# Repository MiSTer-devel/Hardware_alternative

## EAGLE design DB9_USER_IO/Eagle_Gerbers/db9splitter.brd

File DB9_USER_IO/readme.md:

This is an alternative to the USB 3.0 connector. It's a DB9 port, compatible with Genesis
gamepads. Also each pin of the FPGA is protected with BAT54S diodes, so it's not possible
less than 0V or more than 3.3V enter to the FPGA. Included the Genesis core fork.

The cores with DB9 support are available here:
https://github.com/antoniovillena/MiSTer_DB9

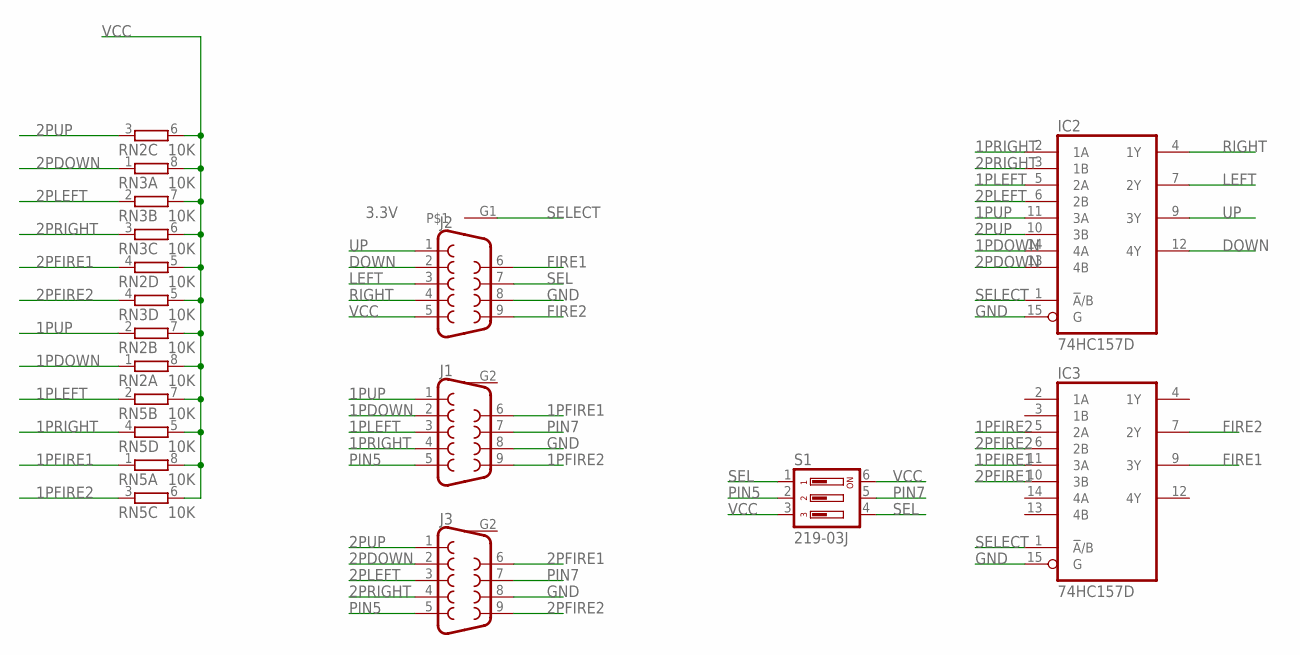
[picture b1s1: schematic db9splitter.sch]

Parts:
IC2, IC3: 74HC157D; SO16
J1, J3: SPARKFUN-CONNECTORS_DB9MALE; SPARKFUN-CONNECTORS_DB9_MALE
J2: DB9FEMALE; DB9
RN2, RN3, RN5: 10K; 0603-ARC
S1: 219-03J; CTS-219-03J

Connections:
1PDOWN: IC2.14 (4A), J1.2, RN2.1
1PFIRE1: IC3.11 (3A), J1.6, RN5.1
1PFIRE2: IC3.5 (2A), J1.9, RN5.3 (1)
1PLEFT: IC2.5 (2A), J1.3, RN5.2 (1)
1PRIGHT: IC2.2 (1A), J1.4, RN5.4 (1)
1PUP: IC2.11 (3A), J1.1, RN2.2 (1)
2PDOWN: IC2.13 (4B), J3.2, RN3.1
2PFIRE1: IC3.10 (3B), J3.6, RN2.4 (1)
2PFIRE2: IC3.6 (2B), J3.9, RN3.4 (1)
2PLEFT: IC2.6 (2B), J3.3, RN3.2 (1)
2PRIGHT: IC2.3 (1B), J3.4, RN3.3 (1)
2PUP: IC2.10 (3B), J3.1, RN2.3 (1)
DOWN: IC2.12 (4Y), J2.2
FIRE1: IC3.9 (3Y), J2.6
FIRE2: IC3.7 (2Y), J2.9
GND: IC2.8 (GND), IC2.15 (G), IC3.8 (GND), IC3.15 (G), J1.8, J2.8, J3.8
LEFT: IC2.7 (2Y), J2.3
PIN5: J1.5, J3.5, S1.2
PIN7: J1.7, J3.7, S1.5
RIGHT: IC2.4 (1Y), J2.4
SEL: J2.7, S1.1, S1.4
SELECT: IC2.1 (!A!/B), IC3.1 (!A!/B), J2.G1
UP: IC2.9 (3Y), J2.1
VCC: IC2.16 (VCC), IC3.16 (VCC), J2.5, RN2.5 (2), RN2.6 (2), RN2.7 (2), RN2.8 (2), RN3.5 (2), RN3.6 (2), RN3.7 (2), RN3.8 (2), RN5.5 (2), RN5.6 (2), RN5.7 (2), RN5.8 (2), S1.3, S1.6

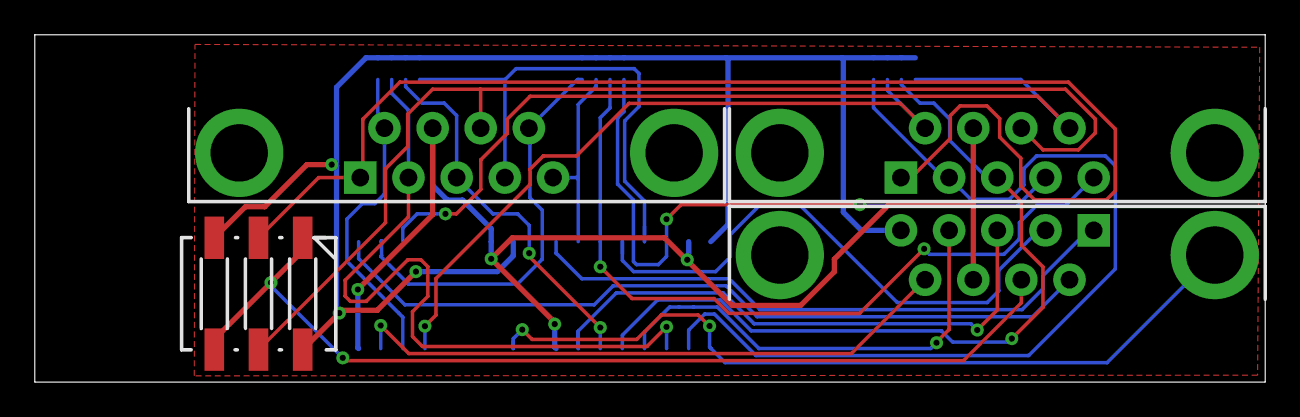
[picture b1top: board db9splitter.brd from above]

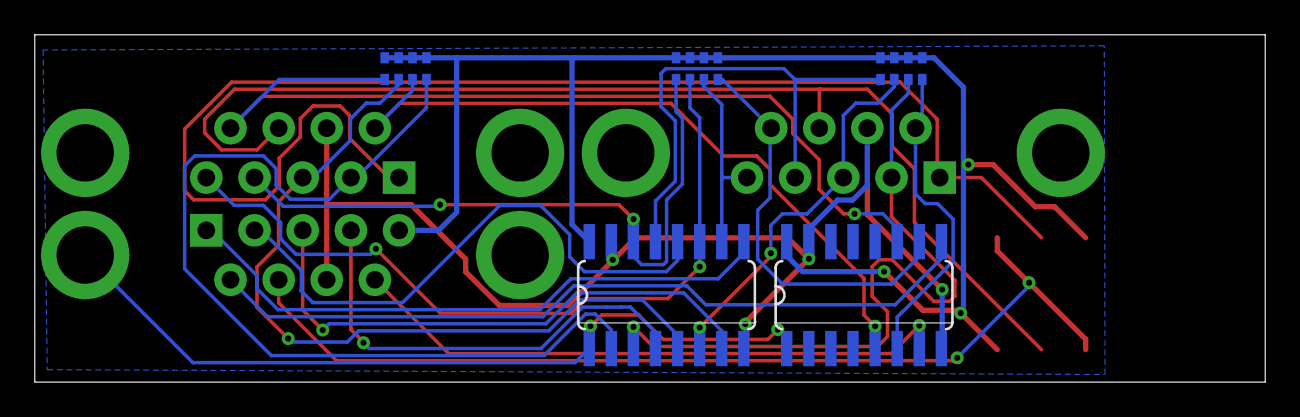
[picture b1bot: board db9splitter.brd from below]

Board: 2 copper layers, 70.7 x 20.0 mm, 9 parts (5 on the bottom side), 24 nets.

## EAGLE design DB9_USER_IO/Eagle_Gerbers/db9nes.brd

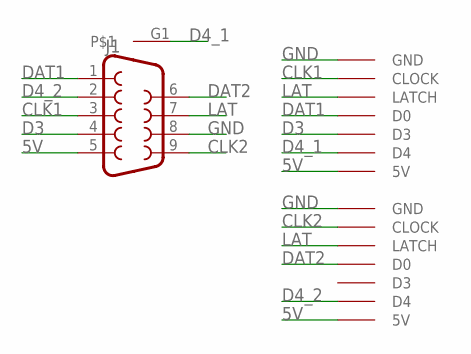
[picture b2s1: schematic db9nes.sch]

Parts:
J1: DB9FEMALE; DB9
U$1, U$2: NESCONNNO_TABS; NESCONN_NO_TABS

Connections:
5V: J1.5, U$1.5V, U$2.5V
CLK1: J1.3, U$2.CLOCK
CLK2: J1.9, U$1.CLOCK
D3: J1.4, U$2.D3
D4_1: J1.G1, U$2.D4
D4_2: J1.2, U$1.D4
DAT1: J1.1, U$2.D0
DAT2: J1.6, U$1.D0
GND: J1.8, U$1.GND, U$2.GND
LAT: J1.7, U$1.LATCH, U$2.LATCH

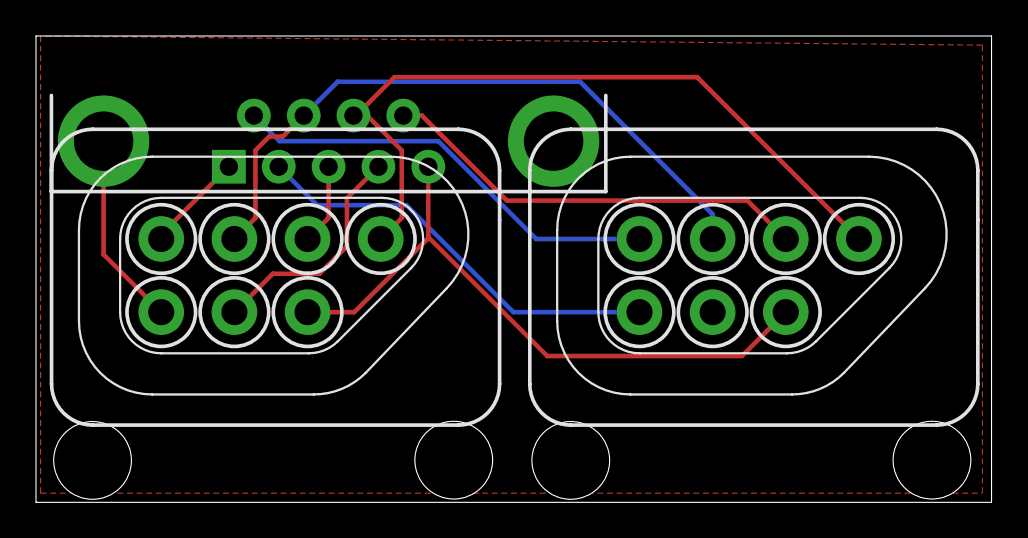
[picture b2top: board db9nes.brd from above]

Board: 2 copper layers, 53.1 x 25.9 mm, 3 parts (0 on the bottom side), 10 nets.

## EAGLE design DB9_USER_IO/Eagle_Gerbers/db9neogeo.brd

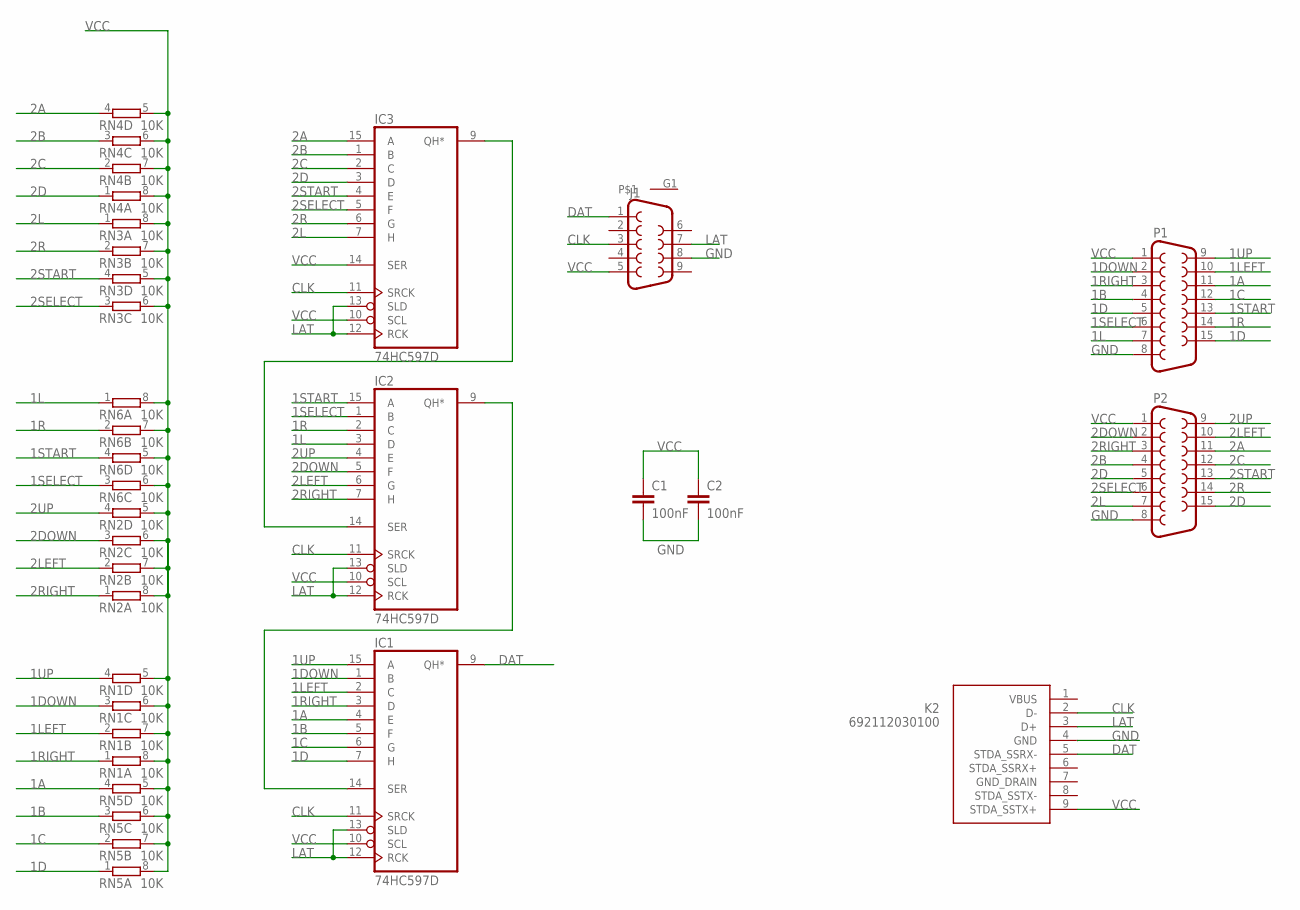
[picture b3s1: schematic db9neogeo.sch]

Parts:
C1, C2: 100nF; C0603K
IC1, IC2, IC3: 74HC597D; SO16
J1: DB9FEMALE; DB9
K2: 692112030100
P1, P2: F15HP
RN1, RN2, RN3, RN4, RN5, RN6: 10K; 0603-ARC

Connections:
1A: IC1.4 (E), P1.11, RN5.4 (1)
1B: IC1.5 (F), P1.4, RN5.3 (1)
1C: IC1.6 (G), P1.12, RN5.2 (1)
1D: IC1.7 (H), P1.5, P1.15, RN5.1
1DOWN: IC1.1 (B), P1.2, RN1.3 (1)
1L: IC2.3 (D), P1.7, RN6.1
1LEFT: IC1.2 (C), P1.10, RN1.2 (1)
1R: IC2.2 (C), P1.14, RN6.2 (1)
1RIGHT: IC1.3 (D), P1.3, RN1.1
1SELECT: IC2.1 (B), P1.6, RN6.3 (1)
1START: IC2.15 (A), P1.13, RN6.4 (1)
1UP: IC1.15 (A), P1.9, RN1.4 (1)
2A: IC3.15 (A), P2.11, RN4.4 (1)
2B: IC3.1 (B), P2.4, RN4.3 (1)
2C: IC3.2 (C), P2.12, RN4.2 (1)
2D: IC3.3 (D), P2.5, P2.15, RN4.1
2DOWN: IC2.5 (F), P2.2, RN2.3 (1)
2L: IC3.7 (H), P2.7, RN3.1
2LEFT: IC2.6 (G), P2.10, RN2.2 (1)
2R: IC3.6 (G), P2.14, RN3.2 (1)
2RIGHT: IC2.7 (H), P2.3, RN2.1
2SELECT: IC3.5 (F), P2.6, RN3.3 (1)
2START: IC3.4 (E), P2.13, RN3.4 (1)
2UP: IC2.4 (E), P2.9, RN2.4 (1)
CLK: IC1.11 (SRCK), IC2.11 (SRCK), IC3.11 (SRCK), J1.3, K2.2 (D-)
DAT: IC1.9 (QH*), J1.1, K2.5 (STDA_SSRX-)
GND: C1.2, C2.2, IC1.8 (GND), IC2.8 (GND), IC3.8 (GND), J1.8, K2.4 (GND), P1.8, P2.8
LAT: IC1.12 (RCK), IC1.13 (SLD), IC2.12 (RCK), IC2.13 (SLD), IC3.12 (RCK), IC3.13 (SLD), J1.7, K2.3 (D+)
unnamed: IC1.14 (SER), IC2.9 (QH*)
unnamed: IC2.14 (SER), IC3.9 (QH*)
VCC: C1.1, C2.1, IC1.10 (SCL), IC1.16 (VCC), IC2.10 (SCL), IC2.16 (VCC), IC3.10 (SCL), IC3.14 (SER), IC3.16 (VCC), J1.5, K2.9 (STDA_SSTX+), P1.1, P2.1, RN1.5 (2), RN1.6 (2), RN1.7 (2), RN1.8 (2), RN2.5 (2), RN2.6 (2), RN2.7 (2), RN2.8 (2), RN3.5 (2), RN3.6 (2), RN3.7 (2), RN3.8 (2), RN4.5 (2), RN4.6 (2), RN4.7 (2), RN4.8 (2), RN5.5 (2), RN5.6 (2), RN5.7 (2), RN5.8 (2), RN6.5 (2), RN6.6 (2), RN6.7 (2), RN6.8 (2)

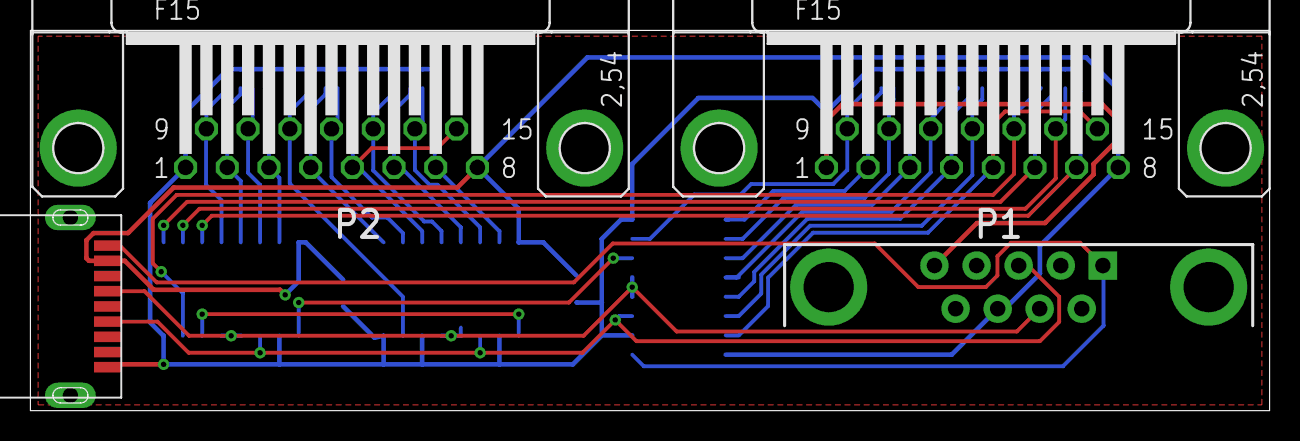
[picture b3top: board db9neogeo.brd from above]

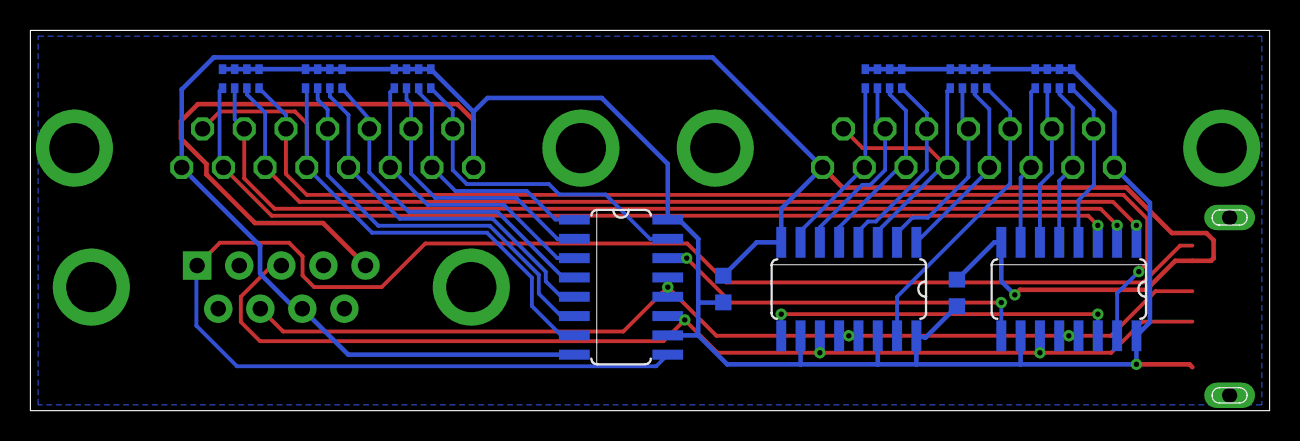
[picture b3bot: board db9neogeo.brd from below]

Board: 2 copper layers, 81.5 x 25.0 mm, 15 parts (11 on the bottom side), 31 nets.

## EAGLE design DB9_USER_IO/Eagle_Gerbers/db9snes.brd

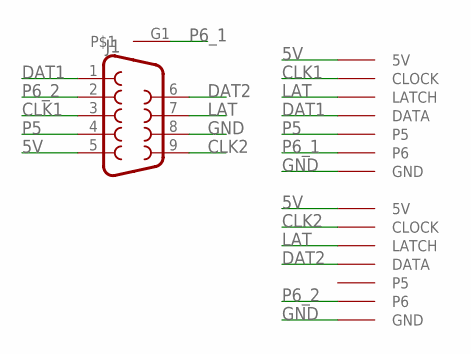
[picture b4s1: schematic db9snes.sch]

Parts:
J1: DB9FEMALE; DB9
U$1, U$3: GAMEPAD-CONN_SNESCONN

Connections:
5V: J1.5, U$1.5V, U$3.5V
CLK1: J1.3, U$3.CLOCK
CLK2: J1.9, U$1.CLOCK
DAT1: J1.1, U$3.DATA
DAT2: J1.6, U$1.DATA
GND: J1.8, U$1.GND, U$3.GND
LAT: J1.7, U$1.LATCH, U$3.LATCH
P5: J1.4, U$3.P5
P6_1: J1.G1, U$3.P6
P6_2: J1.2, U$1.P6

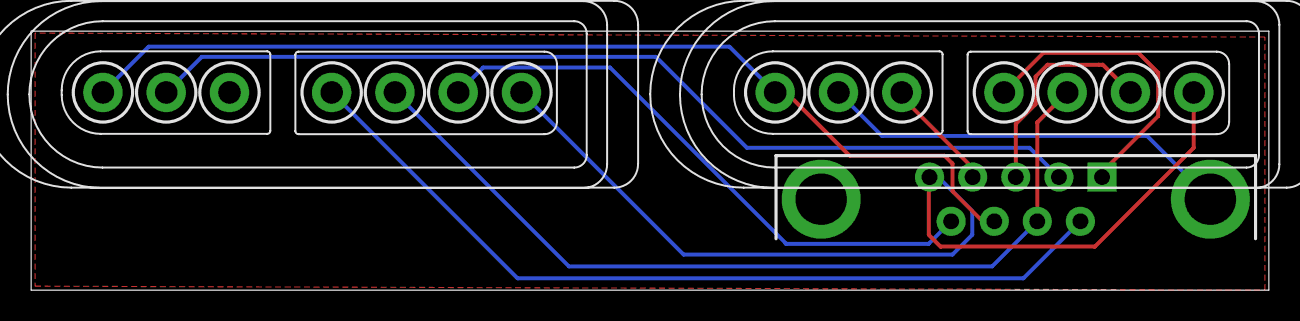
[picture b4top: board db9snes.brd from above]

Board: 2 copper layers, 79.5 x 16.6 mm, 3 parts (0 on the bottom side), 10 nets.

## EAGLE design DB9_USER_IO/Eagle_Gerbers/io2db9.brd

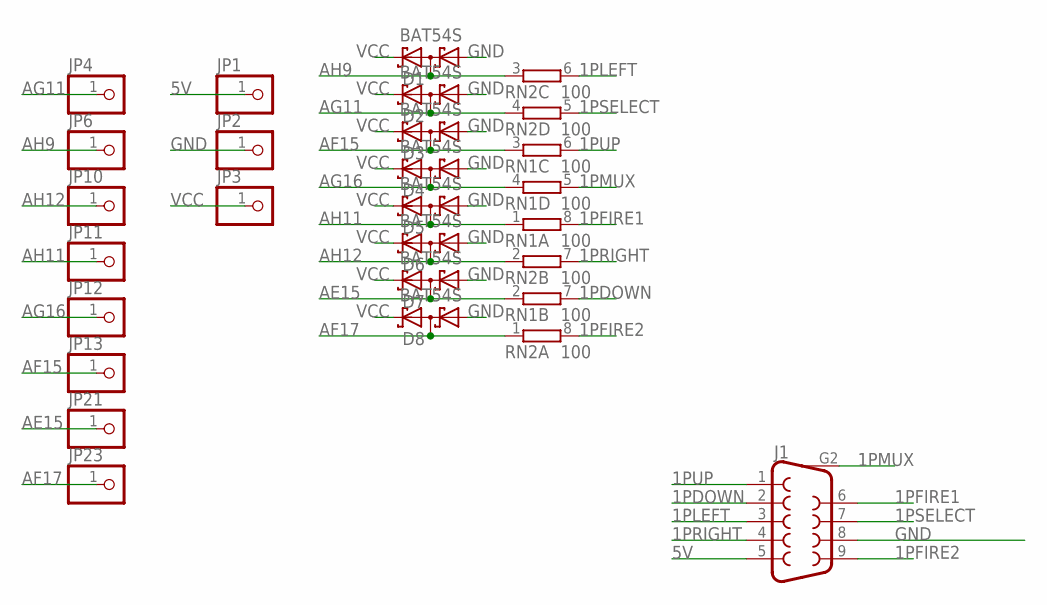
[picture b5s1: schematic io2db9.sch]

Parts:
D1, D2, D3, D4, D5, D6, D7, D8: BAT54S; SOT23
J1: SPARKFUN-CONNECTORS_DB9MALE; SPARKFUN-CONNECTORS_DB9_MALE
JP1, JP2, JP3, JP4, JP6, JP10, JP11, JP12, JP13, JP21, JP23: PINHD-1X1; 1X01
RN1, RN2: 100; 0603-ARC

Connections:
1PDOWN: J1.2, RN1.7 (2)
1PFIRE1: J1.6, RN1.8 (2)
1PFIRE2: J1.9, RN2.8 (2)
1PLEFT: J1.3, RN2.6 (2)
1PMUX: J1.G2 (10), RN1.5 (2)
1PRIGHT: J1.4, RN2.7 (2)
1PSELECT: J1.7, RN2.5 (2)
1PUP: J1.1, RN1.6 (2)
5V: J1.5, JP1.1
AE15: D7.3 (C1A2), JP21.1, RN1.2 (1)
AF15: D3.3 (C1A2), JP13.1, RN1.3 (1)
AF17: D8.3 (C1A2), JP23.1, RN2.1
AG11: D2.3 (C1A2), JP4.1, RN2.4 (1)
AG16: D4.3 (C1A2), JP12.1, RN1.4 (1)
AH9: D1.3 (C1A2), JP6.1, RN2.3 (1)
AH11: D5.3 (C1A2), JP11.1, RN1.1
AH12: D6.3 (C1A2), JP10.1, RN2.2 (1)
GND: D1.1 (A1), D2.1 (A1), D3.1 (A1), D4.1 (A1), D5.1 (A1), D6.1 (A1), D7.1 (A1), D8.1 (A1), J1.8, JP2.1
VCC: D1.2 (C2), D2.2 (C2), D3.2 (C2), D4.2 (C2), D5.2 (C2), D6.2 (C2), D7.2 (C2), D8.2 (C2), JP3.1

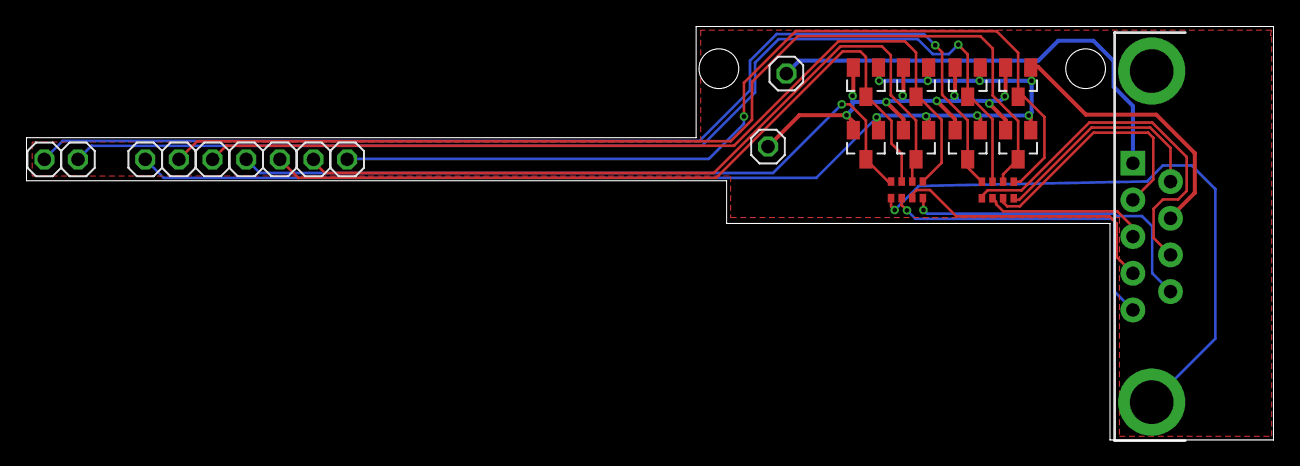
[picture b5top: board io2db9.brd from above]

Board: 2 copper layers, 94.1 x 31.2 mm, 22 parts (0 on the bottom side), 19 nets.

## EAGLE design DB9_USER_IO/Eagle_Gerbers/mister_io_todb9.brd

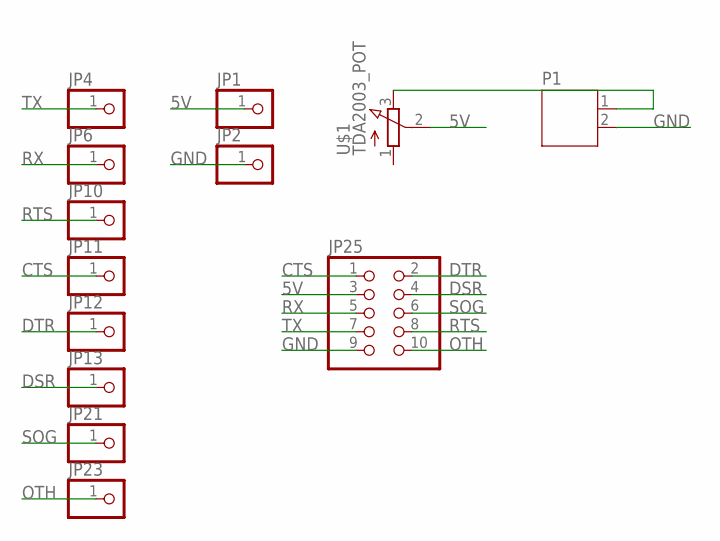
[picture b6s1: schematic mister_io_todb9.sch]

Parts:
JP1, JP2, JP4, JP6, JP10, JP11, JP12, JP13, JP21, JP23: PINHD-1X1; 1X01
JP25: PINHD-2X5; 2X05
P1: JST-PH2
U$1: TDA2003_POT

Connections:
5V: JP1.1, JP25.3, U$1.2 (S)
CTS: JP11.1, JP25.1
DSR: JP13.1, JP25.4
DTR: JP12.1, JP25.2
GND: JP2.1, JP25.9, P1.2
unnamed: P1.1, U$1.3 (E)
OTH: JP23.1, JP25.10
RTS: JP10.1, JP25.8
RX: JP6.1, JP25.5
SOG: JP21.1, JP25.6
TX: JP4.1, JP25.7

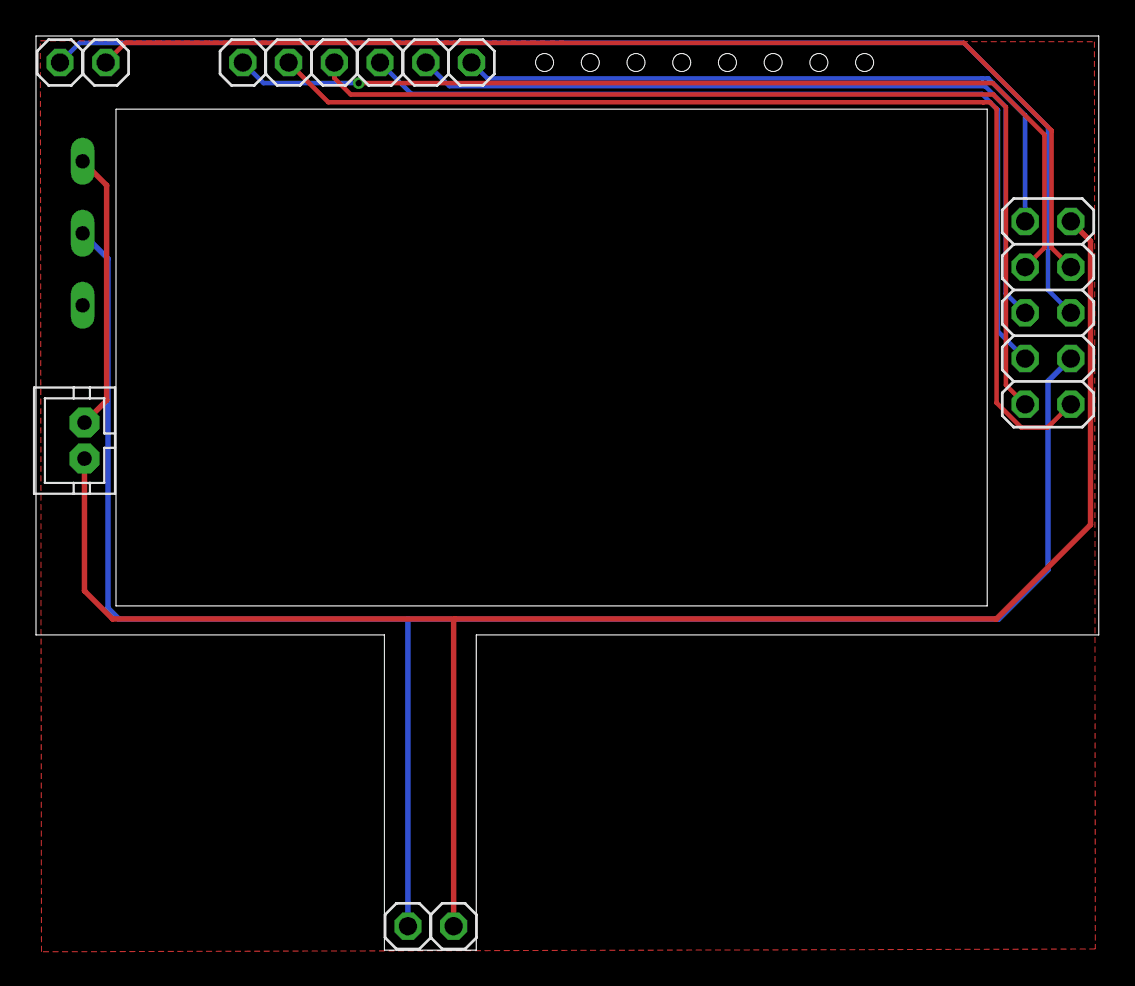
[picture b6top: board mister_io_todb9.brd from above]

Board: 2 copper layers, 59.0 x 50.8 mm, 13 parts (0 on the bottom side), 11 nets.

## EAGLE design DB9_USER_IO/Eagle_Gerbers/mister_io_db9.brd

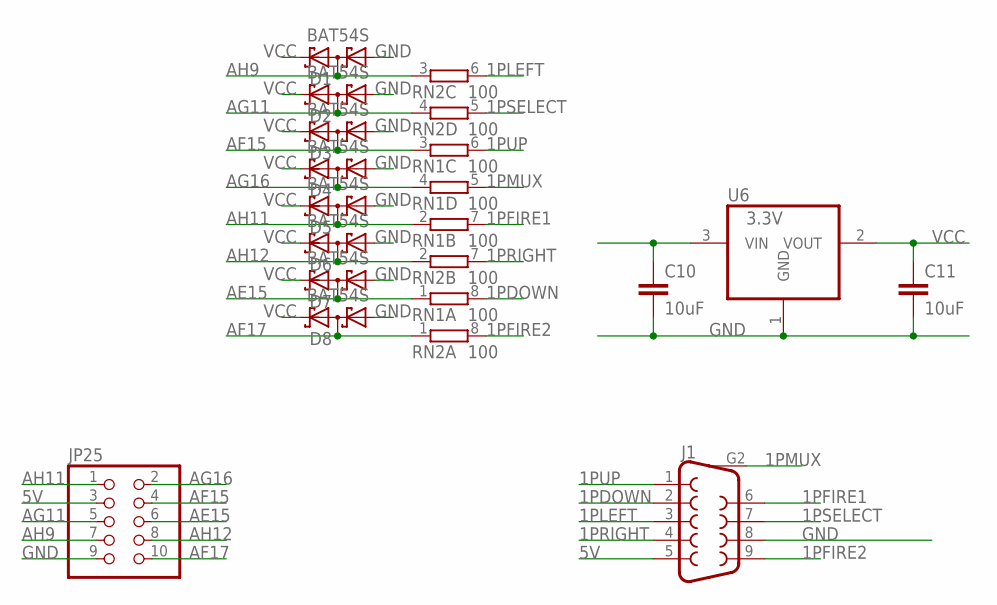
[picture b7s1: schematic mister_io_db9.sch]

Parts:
C10, C11: 10uF; C0603K
D1, D2, D3, D4, D5, D6, D7, D8: BAT54S; SOT23
J1: SPARKFUN-CONNECTORS_DB9MALE; SPARKFUN-CONNECTORS_DB9_MALE
JP25: PINHD-2X5; 2X05
RN1, RN2: 100; 0603-ARC
U6: 3.3V; SOT223

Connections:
1PDOWN: J1.2, RN1.8 (2)
1PFIRE1: J1.6, RN1.7 (2)
1PFIRE2: J1.9, RN2.8 (2)
1PLEFT: J1.3, RN2.6 (2)
1PMUX: J1.G2 (10), RN1.5 (2)
1PRIGHT: J1.4, RN2.7 (2)
1PSELECT: J1.7, RN2.5 (2)
1PUP: J1.1, RN1.6 (2)
5V: C10.1, J1.5, JP25.3, U6.3 (VIN)
AE15: D7.3 (C1A2), JP25.6, RN1.1
AF15: D3.3 (C1A2), JP25.4, RN1.3 (1)
AF17: D8.3 (C1A2), JP25.10, RN2.1
AG11: D2.3 (C1A2), JP25.5, RN2.4 (1)
AG16: D4.3 (C1A2), JP25.2, RN1.4 (1)
AH9: D1.3 (C1A2), JP25.7, RN2.3 (1)
AH11: D5.3 (C1A2), JP25.1, RN1.2 (1)
AH12: D6.3 (C1A2), JP25.8, RN2.2 (1)
GND: C10.2, C11.2, D1.1 (A1), D2.1 (A1), D3.1 (A1), D4.1 (A1), D5.1 (A1), D6.1 (A1), D7.1 (A1), D8.1 (A1), J1.8, JP25.9, U6.1 (GND)
VCC: C11.1, D1.2 (C2), D2.2 (C2), D3.2 (C2), D4.2 (C2), D5.2 (C2), D6.2 (C2), D7.2 (C2), D8.2 (C2), U6.2 (VOUT)

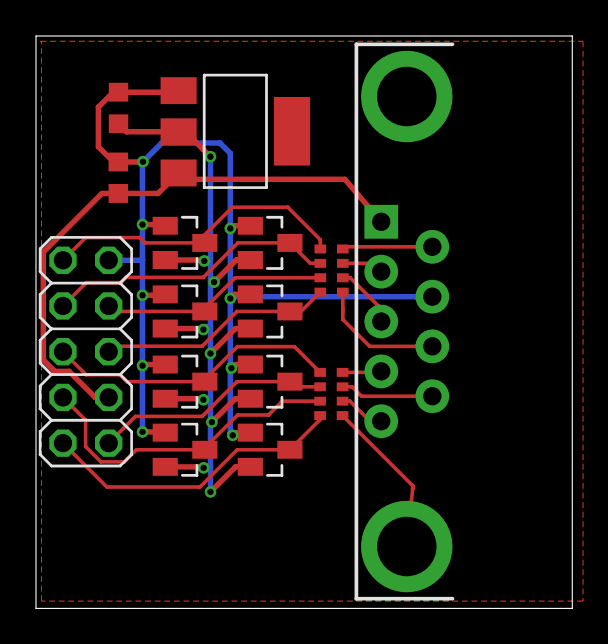
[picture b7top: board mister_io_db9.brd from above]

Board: 2 copper layers, 29.8 x 31.8 mm, 15 parts (0 on the bottom side), 19 nets.

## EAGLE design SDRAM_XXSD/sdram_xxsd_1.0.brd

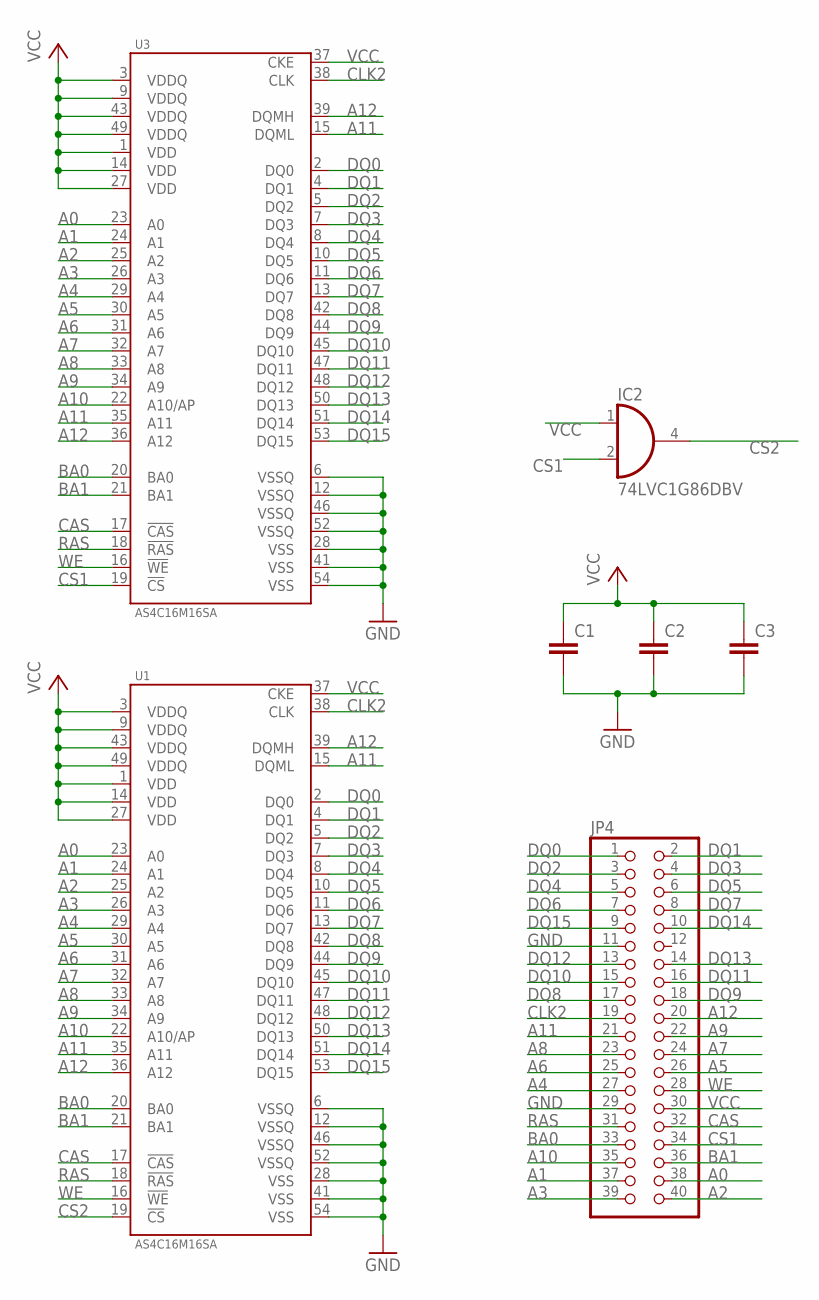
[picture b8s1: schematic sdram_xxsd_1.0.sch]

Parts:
C1, C2, C3: C-EUC0805K; C0805K
IC2: 74LVC1G86DBV; SOT23-5
JP4: PINHD-2X20_2.54-SMD; 2X20SMD
U1, U3: AS4C16M16SA; TSOPII-54

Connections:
A0: JP4.38, U1.23 (A0), U3.23 (A0)
A1: JP4.37, U1.24 (A1), U3.24 (A1)
A2: JP4.40, U1.25 (A2), U3.25 (A2)
A3: JP4.39, U1.26 (A3), U3.26 (A3)
A4: JP4.27, U1.29 (A4), U3.29 (A4)
A5: JP4.26, U1.30 (A5), U3.30 (A5)
A6: JP4.25, U1.31 (A6), U3.31 (A6)
A7: JP4.24, U1.32 (A7), U3.32 (A7)
A8: JP4.23, U1.33 (A8), U3.33 (A8)
A9: JP4.22, U1.34 (A9), U3.34 (A9)
A10: JP4.35, U1.22 (A10/AP), U3.22 (A10/AP)
A11: JP4.21, U1.15 (DQML), U1.35 (A11), U3.15 (DQML), U3.35 (A11)
A12: JP4.20, U1.36 (A12), U1.39 (DQMH), U3.36 (A12), U3.39 (DQMH)
BA0: JP4.33, U1.20 (BA0), U3.20 (BA0)
BA1: JP4.36, U1.21 (BA1), U3.21 (BA1)
CAS: JP4.32, U1.17 (!CAS), U3.17 (!CAS)
CLK2: JP4.19, U1.38 (CLK), U3.38 (CLK)
CS1: IC2.2 (I1), JP4.34, U3.19 (!CS)
CS2: IC2.4 (O), U1.19 (!CS)
DQ0: JP4.1, U1.2 (DQ0), U3.2 (DQ0)
DQ1: JP4.2, U1.4 (DQ1), U3.4 (DQ1)
DQ2: JP4.3, U1.5 (DQ2), U3.5 (DQ2)
DQ3: JP4.4, U1.7 (DQ3), U3.7 (DQ3)
DQ4: JP4.5, U1.8 (DQ4), U3.8 (DQ4)
DQ5: JP4.6, U1.10 (DQ5), U3.10 (DQ5)
DQ6: JP4.7, U1.11 (DQ6), U3.11 (DQ6)
DQ7: JP4.8, U1.13 (DQ7), U3.13 (DQ7)
DQ8: JP4.17, U1.42 (DQ8), U3.42 (DQ8)
DQ9: JP4.18, U1.44 (DQ9), U3.44 (DQ9)
DQ10: JP4.15, U1.45 (DQ10), U3.45 (DQ10)
DQ11: JP4.16, U1.47 (DQ11), U3.47 (DQ11)
DQ12: JP4.13, U1.48 (DQ12), U3.48 (DQ12)
DQ13: JP4.14, U1.50 (DQ13), U3.50 (DQ13)
DQ14: JP4.10, U1.51 (DQ14), U3.51 (DQ14)
DQ15: JP4.9, U1.53 (DQ15), U3.53 (DQ15)
GND: C1.2, C2.2, C3.2, IC2.3 (GND), JP4.11, JP4.29, U1.6 (VSSQ), U1.12 (VSSQ), U1.28 (VSS), U1.41 (VSS), U1.46 (VSSQ), U1.52 (VSSQ), U1.54 (VSS), U3.6 (VSSQ), U3.12 (VSSQ), U3.28 (VSS), U3.41 (VSS), U3.46 (VSSQ), U3.52 (VSSQ), U3.54 (VSS)
RAS: JP4.31, U1.18 (!RAS), U3.18 (!RAS)
VCC: C1.1, C2.1, C3.1, IC2.1 (I0), IC2.5 (VCC), JP4.30, U1.1 (VDD), U1.3 (VDDQ), U1.9 (VDDQ), U1.14 (VDD), U1.27 (VDD), U1.37 (CKE), U1.43 (VDDQ), U1.49 (VDDQ), U3.1 (VDD), U3.3 (VDDQ), U3.9 (VDDQ), U3.14 (VDD), U3.27 (VDD), U3.37 (CKE), U3.43 (VDDQ), U3.49 (VDDQ)
WE: JP4.28, U1.16 (!WE), U3.16 (!WE)

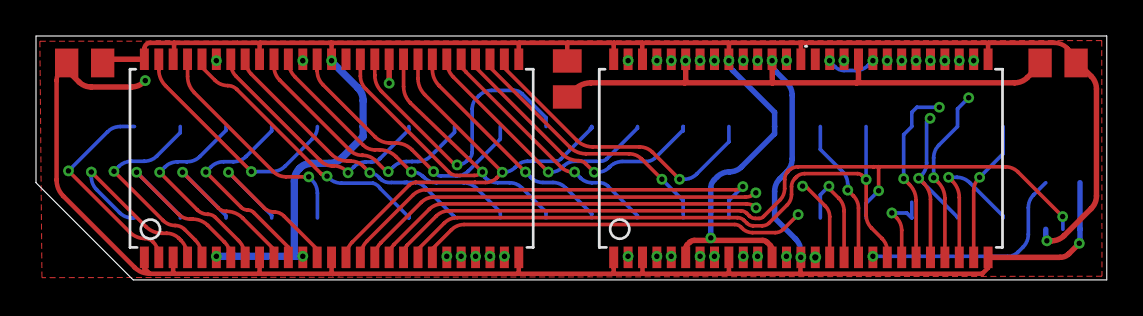
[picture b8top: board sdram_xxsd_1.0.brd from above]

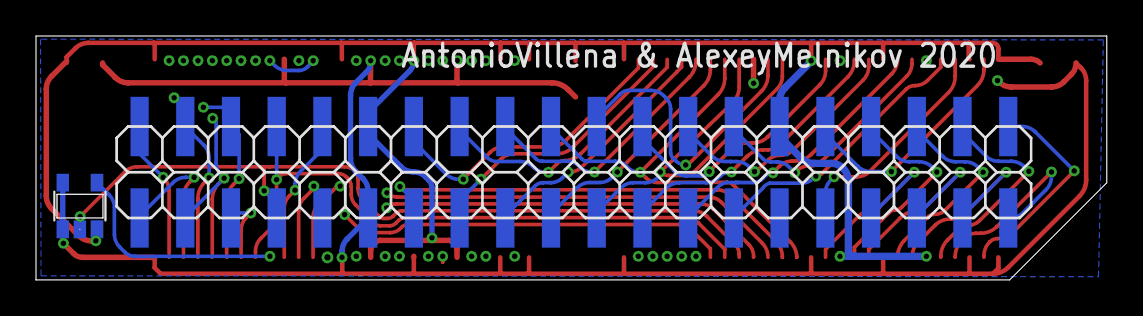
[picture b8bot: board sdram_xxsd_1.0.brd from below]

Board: 4 copper layers, 59.5 x 13.6 mm, 7 parts (2 on the bottom side), 39 nets.

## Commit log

2019-11-13 Added DB9 hardware and core
2019-11-14 Upgrade to latest version
2019-11-17 Initial commit Minimig
2019-11-17 Changes for DB9 support
2019-11-17 Initial commit C64
2019-11-17 Moved cores to this repository: https://github.com/antoniovillena/MiSTer_DB9
2019-11-17 Correction on readme.md
2019-11-26 Added DB9 to Neo Geo adapter
2019-12-04 New picture for XXSD128
2019-12-16 New board to add DB9 on official IOs. Unfinished routing
2019-12-16 Routed finished. Added gerbers
2020-01-09 db9 splitter added
2020-01-16 Change splitter by 74HC157 circuit
2020-01-26 updated db9neogeo with usb3 input. added db9neogeo
2020-01-26 added db9nes
2020-01-31 updated db9splitter
2020-02-01 removed DB9_USER_IO

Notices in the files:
parts and their libraries:
SparkFun-Connectors: Licensing: Creative Commons ShareAlike 4.0 International - https://creativecommons.org/licenses/by-sa/4.0
Wuerth_Elektronik_eiCan_Communication_Co: Copyright: Würth Elektronik
